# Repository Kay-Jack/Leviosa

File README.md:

# Photon

## Description

## Complete

## WIP

## Features

## Images
### PCB Front View

### PCB Back View

### Schematic 

## Version

## Repository
Hosted on GitHub: [AirMatress/Photon](https://github.com/AirMatress/Photon)

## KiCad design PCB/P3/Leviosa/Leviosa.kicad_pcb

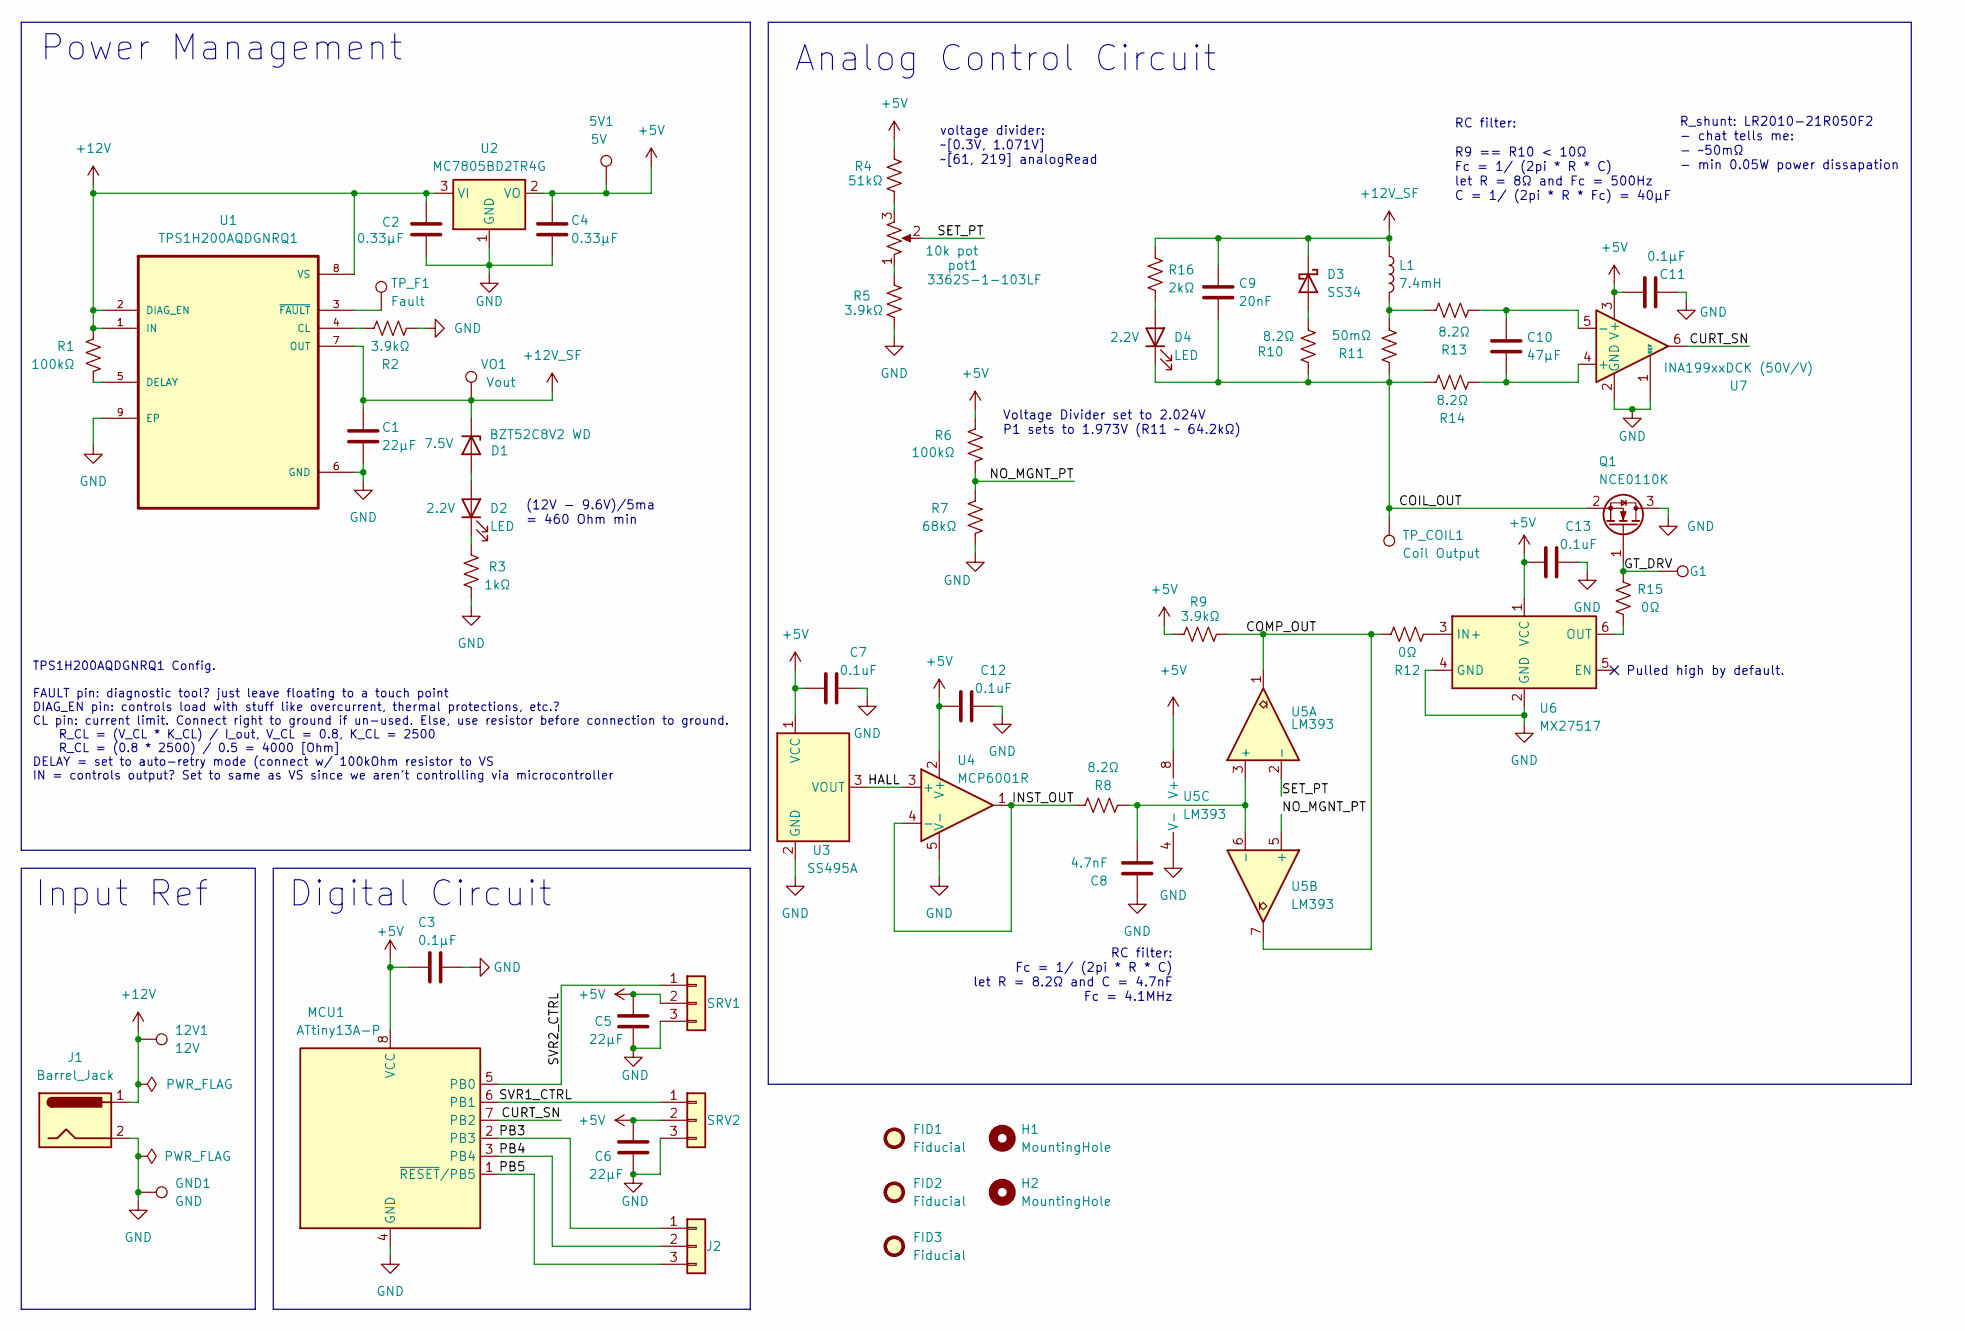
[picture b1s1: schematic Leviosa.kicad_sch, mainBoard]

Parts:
5V1: 5V; TestPoint_Pad_D1.5mm
12V1: 12V; TestPoint_Pad_D1.0mm
C1, C5, C6: 22µF; C_0805_2012Metric
C2, C4: 0.33µF; C_0805_2012Metric
C3, C11: 0.1µF; C_0603_1608Metric
C7, C12, C13: 0.1uF; C_0603_1608Metric
C8: 4.7nF; C_0805_2012Metric_Pad1.18x1.45mm_HandSolder
C9: 20nF; C_0805_2012Metric_Pad1.18x1.45mm_HandSolder
C10: 47μF; C_1206_3216Metric
D1: BZT52C8V2 WD; D_SOD-123
D2, D4: LED; LED_0805_2012Metric; PARTREV 16
D3: SS34; D_SOD-323
FID1, FID2, FID3: Fiducial; Fiducial_0.5mm_Mask1mm
G1: set_point_trigger; TestPoint_Pad_D1.0mm
GND1: GND; TestPoint_Pad_D1.0mm
H1, H2: MountingHole; MountingHole_3.2mm_M3_ISO7380
J1: Barrel_Jack; BarrelJack_Kycon_KLDX-0202-xC_Horizontal
J2: 2.54mm 1x03 Spare; PinHeader_1x03_P2.54mm_Vertical
L1: 7.4mH; PinHeader_2x01_P2.54mm_Vertical
MCU1: ATtiny13A-P; DIP-8_W7.62mm
Q1: NCE0110K; TO-252-2
R1, R6: 100kΩ; R_0603_1608Metric
R2, R5, R9: 3.9kΩ; R_0603_1608Metric
R3: 1kΩ; R_0603_1608Metric
R4: 51kΩ; R_0603_1608Metric
R7: 68kΩ; R_0603_1608Metric
R8, R10, R13, R14: 8.2Ω; R_1206_3216Metric
R11: 50mΩ; R_2010_5025Metric
R12, R15: 0Ω; R_0603_1608Metric
R16: 2kΩ; R_0603_1608Metric
SRV1, SRV2: 2.54mm 1x03 Servo 1; PinHeader_1x03_P2.54mm_Vertical
TP_COIL1: Coil Output; TestPoint_Pad_D1.0mm
TP_F1: Fault; TestPoint_Pad_D1.0mm
U1: TPS1H200AQDGNRQ1; SOP65P490X110-9N
U2: MC7805BD2TR4G; TO-263-2
U3: SS495A; PinHeader_1x03_P2.54mm_Vertical
U4: MCP6001R; SOT-23-5
U5: LM393; SOIC-8_3.9x4.9mm_P1.27mm
U6: MX27517; SOT-23-6
U7: INA199xxDCK (50V/V); SOT-363_SC-70-6
VO1: Vout; TestPoint_Pad_D1.0mm
pot1: 3362S-1-103LF; Potentiometer_ACP_CA6-H2,5_Horizontal

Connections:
+5V: 5V1.1, C3.1, C4.1, C5.1, C6.1, C7.1, C11.1, C12.1, C13.1, MCU1.8 (VCC), R4.2, R6.2, R9.2, SRV1.2, SRV2.2, U2.2 (VO), U3.1 (VCC), U4.2 (V+), U5.8 (V+), U6.1 (VCC), U7.3 (V+)
+12V: 12V1.1, C2.1, J1.1, R1.2, U1.1 (IN), U1.2 (DIAG_EN), U1.8 (VS), U2.3 (VI)
+12V_SF: C1.1, C9.1, D1.1 (K), D3.1 (K), L1.1, R16.1, U1.7 (OUT), VO1.1
/COIL_OUT: C9.2, D4.1 (K), Q1.2 (S), R10.2, R11.2, R14.1, TP_COIL1.1
/COMP_OUT: R9.1, R12.1, U5.1, U5.7
/CURT_SN: MCU1.7 (PB2), U7.6
/GT_DRV: G1.1, Q1.1 (G), R15.2
/HALL: U3.3 (VOUT), U4.3 (+)
/INST_OUT: R8.1, U4.1, U4.4 (-)
/NO_MGNT_PT: R6.1, R7.2, U5.5 (+)
/PB3: J2.1, MCU1.2 (PB3)
/PB4: J2.2, MCU1.3 (PB4)
/PB5: J2.3, MCU1.1 (~RESET/PB5)
/SET_PT: U5.2 (-), pot1.2
/SVR1_CTRL: MCU1.6 (PB1), SRV2.1
/SVR2_CTRL: MCU1.5 (PB0), SRV1.1
GND: C1.2, C2.2, C3.2, C4.2, C5.2, C6.2, C7.2, C8.1, C11.2, C12.2, C13.2, GND1.1, J1.2, MCU1.4 (GND), Q1.3 (D), R2.1, R3.2, R5.1, R7.1, SRV1.3, SRV2.3, U1.6 (GND), U1.9 (EP), U2.1 (GND), U3.2 (GND), U4.5 (V-), U5.4 (V-), U6.2 (GND), U6.4 (GND), U7.1 (REF), U7.2 (GND)
unnamed: D1.2 (A), D2.2 (A)
unnamed: D2.1 (K), R3.1
unnamed: D3.2 (A), R10.1
unnamed: D4.2 (A), R16.2
unnamed: L1.2, R11.1, R13.1
unnamed: R4.1, pot1.3
unnamed: R5.2, pot1.1
unnamed: R2.2, U1.4 (CL)
unnamed: R1.1, U1.5 (DELAY)
unnamed: TP_F1.1, U1.3 (~FAULT)
unnamed: C8.2, R8.2, U5.3 (+), U5.6 (-)
unnamed: R12.2, U6.3 (IN+)
unnamed: R15.1, U6.6 (OUT)
unnamed: C10.1, R14.2, U7.4 (+)
unnamed: C10.2, R13.2, U7.5 (-)

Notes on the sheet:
Power Management
RC filter: R9 == R10 < 10Ω Fc = 1/ (2pi * R * C) let R = 8Ω and Fc = 500Hz C = 1/ (2pi * R * Fc) = 40μF
R_shunt: LR2010-21R050F2 - chat tells me: - ~50mΩ - min 0.05W power dissapation
Input Ref
Analog Control Circuit
(12V - 9.6V)/5ma = 460 Ohm min
TPS1H200AQDGNRQ1 Config. FAULT pin: diagnostic tool? just leave floating to a touch point DIAG_EN pin: controls load with stuff like overcurrent, thermal protections, etc.? CL pin: current limit. Connect right to ground if un-used. Else, use resistor before connection to ground. R_CL = (V_CL * K_CL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
Digital Circuit
Pulled high by default.
voltage divider: ~[0.3V, 1.071V] ~[61, 219] analogRead
RC filter: Fc = 1/ (2pi * R * C) let R = 8.2Ω and C = 4.7nF Fc = 4.1MHz
Voltage Divider set to 2.024V P1 sets to 1.973V (R11 ~ 64.2kΩ)

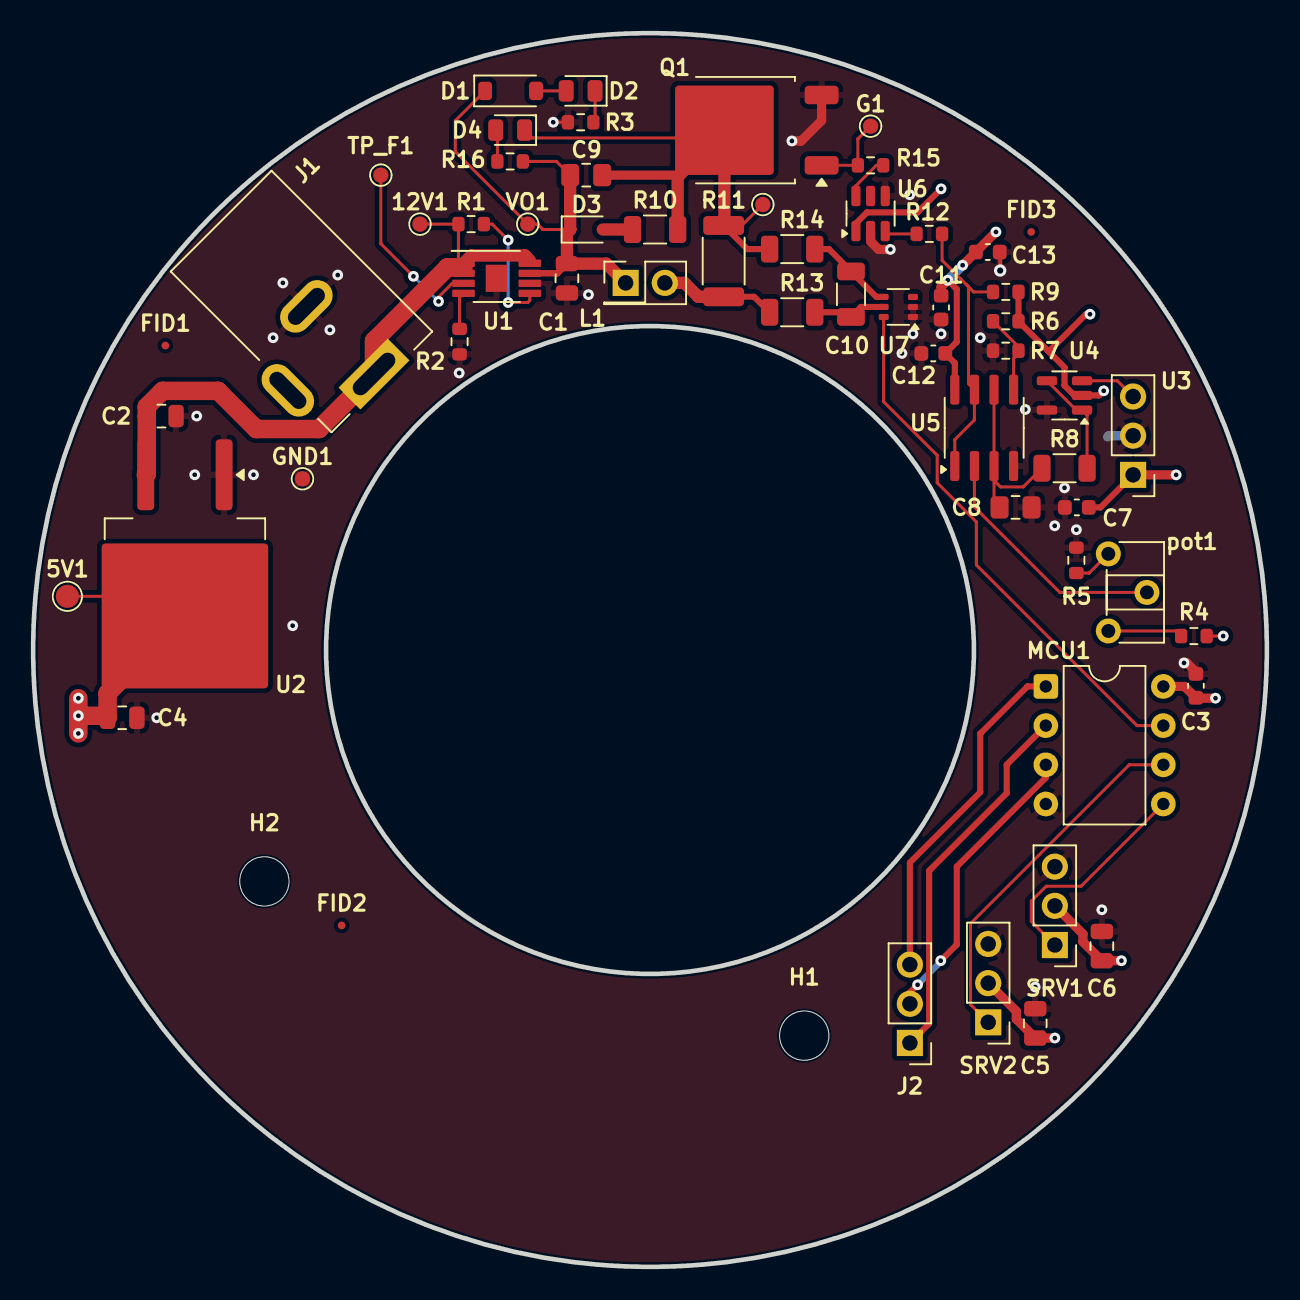
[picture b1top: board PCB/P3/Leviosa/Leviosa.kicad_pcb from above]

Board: 2 copper layers, 80.0 x 80.0 mm, 60 parts (0 on the bottom side), 32 nets.

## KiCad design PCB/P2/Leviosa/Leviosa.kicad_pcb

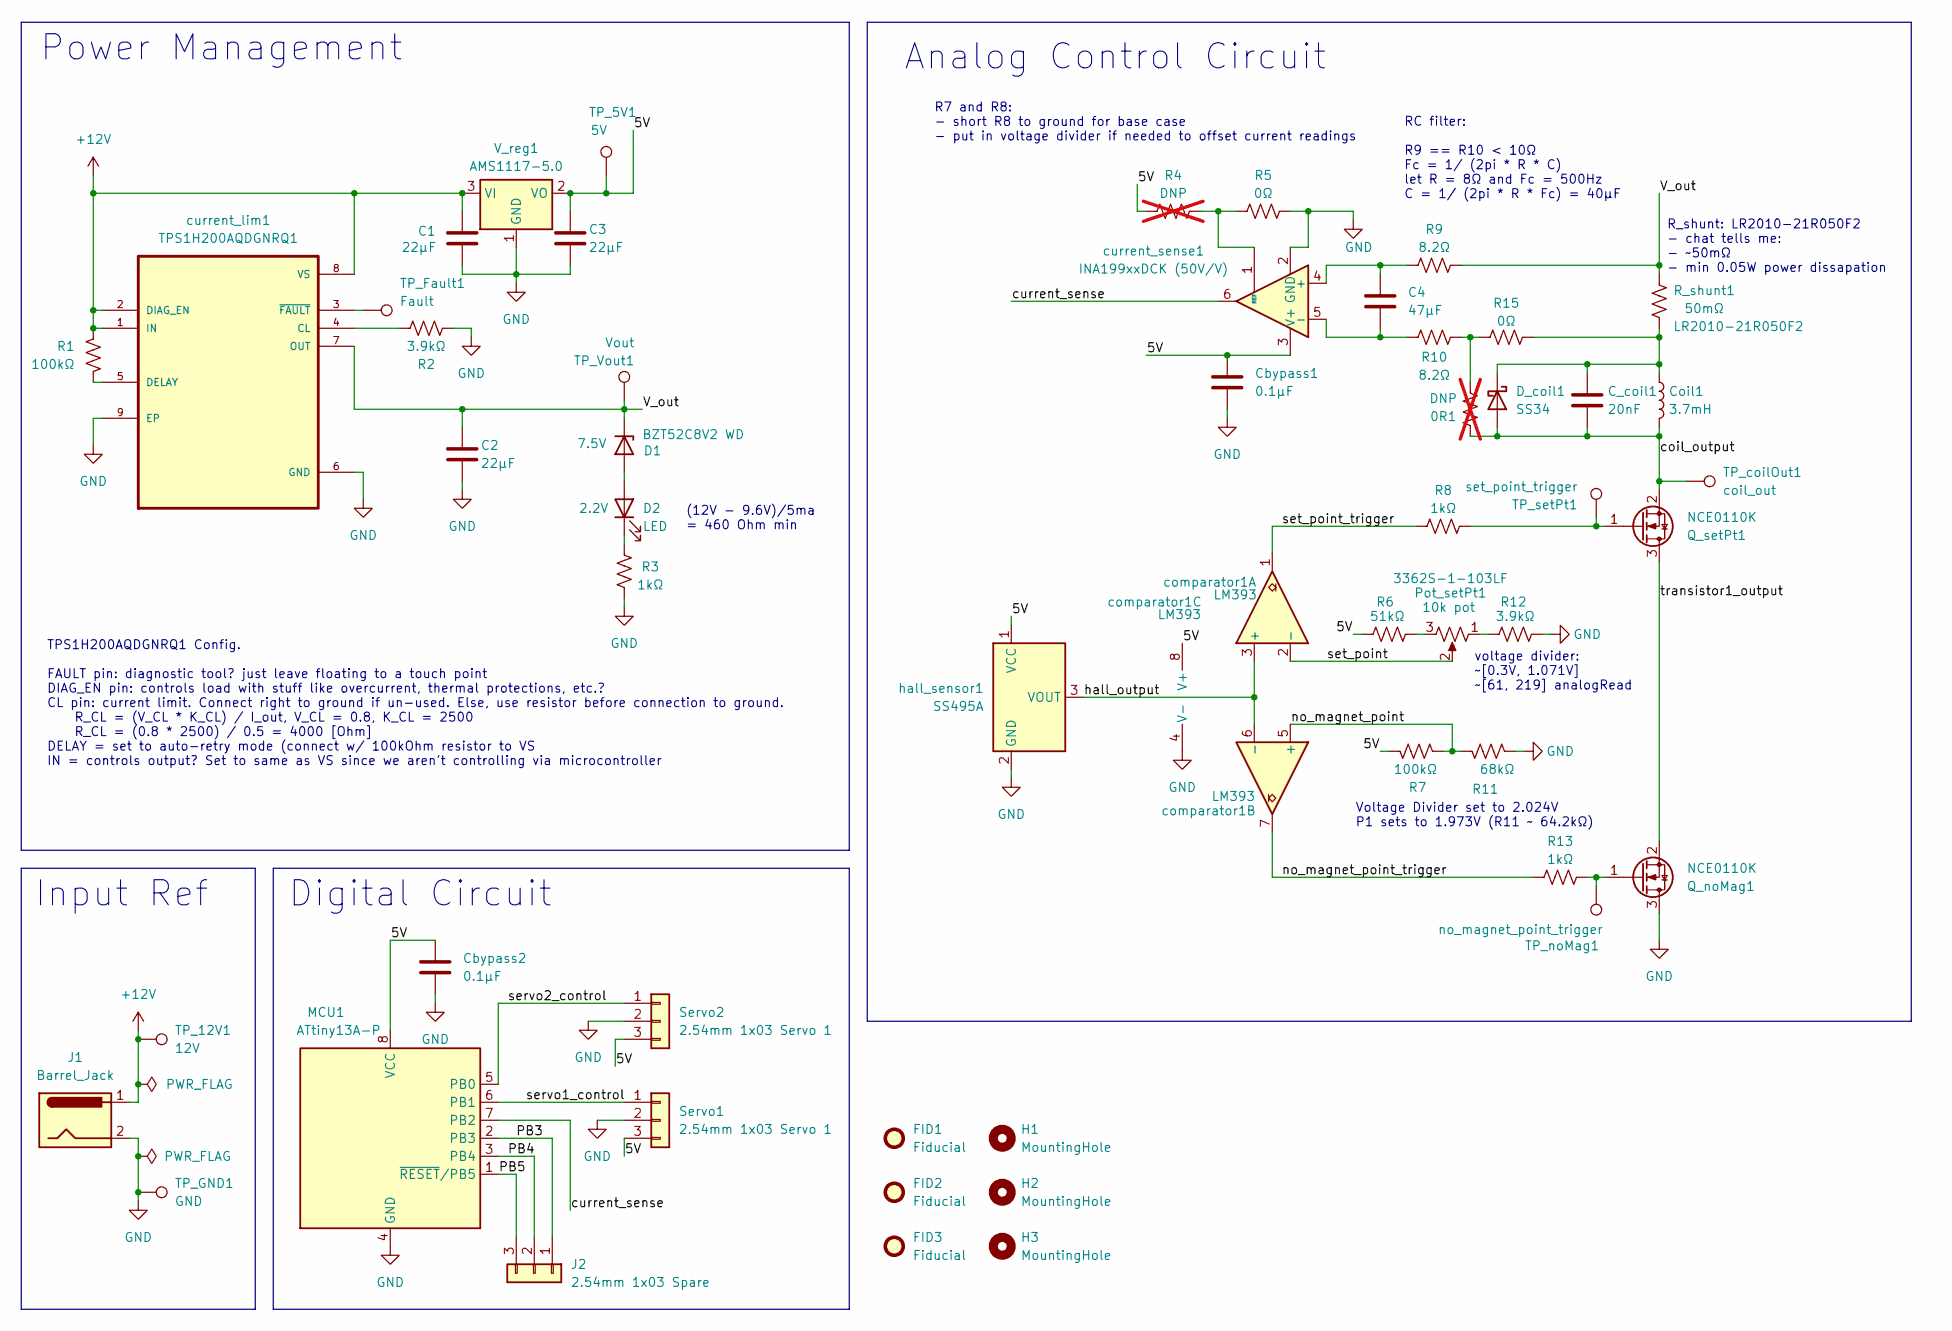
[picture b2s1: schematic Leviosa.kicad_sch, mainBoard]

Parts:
0R1: DNP; R_0603_1608Metric; not fitted
C1, C2, C3: 22µF; C_0805_2012Metric
C4: 47μF; C_1206_3216Metric
C_coil1: 20nF; C_0805_2012Metric_Pad1.18x1.45mm_HandSolder
Cbypass1, Cbypass2: 0.1µF; C_0402_1005Metric
Coil1: 3.7mH; L_Axial_L5.0mm_D3.6mm_P10.00mm_Horizontal_Murata_BL01RN1A2A2
D1: BZT52C8V2 WD; D_SOD-123
D2: LED; LED_0805_2012Metric; PARTREV 16
D_coil1: SS34; D_SMA
FID1, FID2, FID3: Fiducial; Fiducial_0.5mm_Mask1mm
H1, H2, H3: MountingHole; MountingHole_3.2mm_M3_ISO7380
J1: Barrel_Jack; BarrelJack_Kycon_KLDX-0202-xC_Horizontal
J2: 2.54mm 1x03 Spare; PinHeader_1x03_P2.54mm_Vertical
MCU1: ATtiny13A-P; DIP-8_W7.62mm
Pot_setPt1: 3362S-1-103LF; Potentiometer_ACP_CA6-H2,5_Horizontal
Q_noMag1: NCE0110K; TO-252-2
Q_setPt1: NCE0110K; TO-252-2
R1, R7: 100kΩ; R_0805_2012Metric_Pad1.20x1.40mm_HandSolder
R2, R12: 3.9kΩ; R_0603_1608Metric
R3, R8, R13: 1kΩ; R_0805_2012Metric_Pad1.20x1.40mm_HandSolder
R4: DNP; R_0603_1608Metric; not fitted
R5, R15: 0Ω; R_0603_1608Metric
R6: 51kΩ; R_0603_1608Metric
R9, R10: 8.2Ω; R_1206_3216Metric
R11: 68kΩ; R_0603_1608Metric
R_shunt1: 50mΩ; R_2010_5025Metric
Servo1, Servo2: 2.54mm 1x03 Servo 1; PinHeader_1x03_P2.54mm_Vertical
TP_5V1: 5V; TestPoint_Pad_D1.5mm
TP_12V1: 12V; TestPoint_Pad_D1.5mm
TP_Fault1: Fault; TestPoint_Pad_D1.5mm
TP_GND1: GND; TestPoint_Pad_D1.5mm
TP_Vout1: Vout; TestPoint_Pad_D1.5mm
TP_coilOut1: coil_out; TestPoint_Pad_D1.5mm
TP_noMag1: no_magnet_point_trigger; TestPoint_Pad_D1.5mm
TP_setPt1: set_point_trigger; TestPoint_Pad_D1.5mm
V_reg1: AMS1117-5.0; SOT-223-3_TabPin2
comparator1: LM393; SOIC-8_5.3x5.3mm_P1.27mm
current_lim1: TPS1H200AQDGNRQ1; SOP65P490X110-9N
current_sense1: INA199xxDCK (50V/V); SOT-363_SC-70-6
hall_sensor1: SS495A; PinHeader_1x03_P2.54mm_Vertical

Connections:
+12V: C1.1, J1.1, R1.2, TP_12V1.1, V_reg1.3 (VI), current_lim1.1 (IN), current_lim1.2 (DIAG_EN), current_lim1.8 (VS)
/5V: C3.1, Cbypass1.1, Cbypass2.1, MCU1.8 (VCC), R4.2, R6.2, R7.2, Servo1.3, Servo2.3, TP_5V1.1, V_reg1.2 (VO), comparator1.8 (V+), current_sense1.3 (V+), hall_sensor1.1 (VCC)
/PB3: J2.1, MCU1.2 (PB3)
/PB4: J2.2, MCU1.3 (PB4)
/PB5: J2.3, MCU1.1 (~RESET/PB5)
/V_out: C2.1, D1.1 (K), R9.1, R_shunt1.2, TP_Vout1.1, current_lim1.7 (OUT)
/coil_output: 0R1.2, C_coil1.2, Coil1.2, D_coil1.2 (A), Q_setPt1.2 (S), TP_coilOut1.1
/current_sense: MCU1.7 (PB2), current_sense1.6
/hall_output: comparator1.3 (+), comparator1.6 (-), hall_sensor1.3 (VOUT)
/no_magnet_point: R7.1, R11.2, comparator1.5 (+)
/no_magnet_point_trigger: R13.2, comparator1.7
/servo1_control: MCU1.6 (PB1), Servo1.1
/servo2_control: MCU1.5 (PB0), Servo2.1
/set_point: Pot_setPt1.2, comparator1.2 (-)
/set_point_trigger: R8.2, comparator1.1
/transistor1_output: Q_noMag1.2 (S), Q_setPt1.3 (D)
GND: C1.2, C2.2, C3.2, Cbypass1.2, Cbypass2.2, J1.2, MCU1.4 (GND), Q_noMag1.3 (D), R2.1, R3.2, R5.1, R11.1, R12.1, Servo1.2, Servo2.2, TP_GND1.1, V_reg1.1 (GND), comparator1.4 (V-), current_lim1.6 (GND), current_lim1.9 (EP), current_sense1.2 (GND), hall_sensor1.2 (GND)
unnamed: 0R1.1, R10.1, R15.2
unnamed: D1.2 (A), D2.2 (A)
unnamed: D2.1 (K), R3.1
unnamed: C_coil1.1, Coil1.1, D_coil1.1 (K), R15.1, R_shunt1.1
unnamed: Pot_setPt1.1, R12.2
unnamed: Pot_setPt1.3, R6.1
unnamed: Q_noMag1.1 (G), R13.1, TP_noMag1.1
unnamed: Q_setPt1.1 (G), R8.1, TP_setPt1.1
unnamed: R2.2, current_lim1.4 (CL)
unnamed: R1.1, current_lim1.5 (DELAY)
unnamed: TP_Fault1.1, current_lim1.3 (~FAULT)
unnamed: C4.1, R9.2, current_sense1.4 (+)
unnamed: C4.2, R10.2, current_sense1.5 (-)
unnamed: R4.1, R5.2, current_sense1.1 (REF)

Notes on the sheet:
Power Management
RC filter: R9 == R10 < 10Ω Fc = 1/ (2pi * R * C) let R = 8Ω and Fc = 500Hz C = 1/ (2pi * R * Fc) = 40μF
R_shunt: LR2010-21R050F2 - chat tells me: - ~50mΩ - min 0.05W power dissapation
Input Ref
R7 and R8: - short R8 to ground for base case - put in voltage divider if needed to offset current readings
Analog Control Circuit
(12V - 9.6V)/5ma = 460 Ohm min
TPS1H200AQDGNRQ1 Config. FAULT pin: diagnostic tool? just leave floating to a touch point DIAG_EN pin: controls load with stuff like overcurrent, thermal protections, etc.? CL pin: current limit. Connect right to ground if un-used. Else, use resistor before connection to ground. R_CL = (V_CL * K_CL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
Digital Circuit
Voltage Divider set to 2.024V P1 sets to 1.973V (R11 ~ 64.2kΩ)
voltage divider: ~[0.3V, 1.071V] ~[61, 219] analogRead

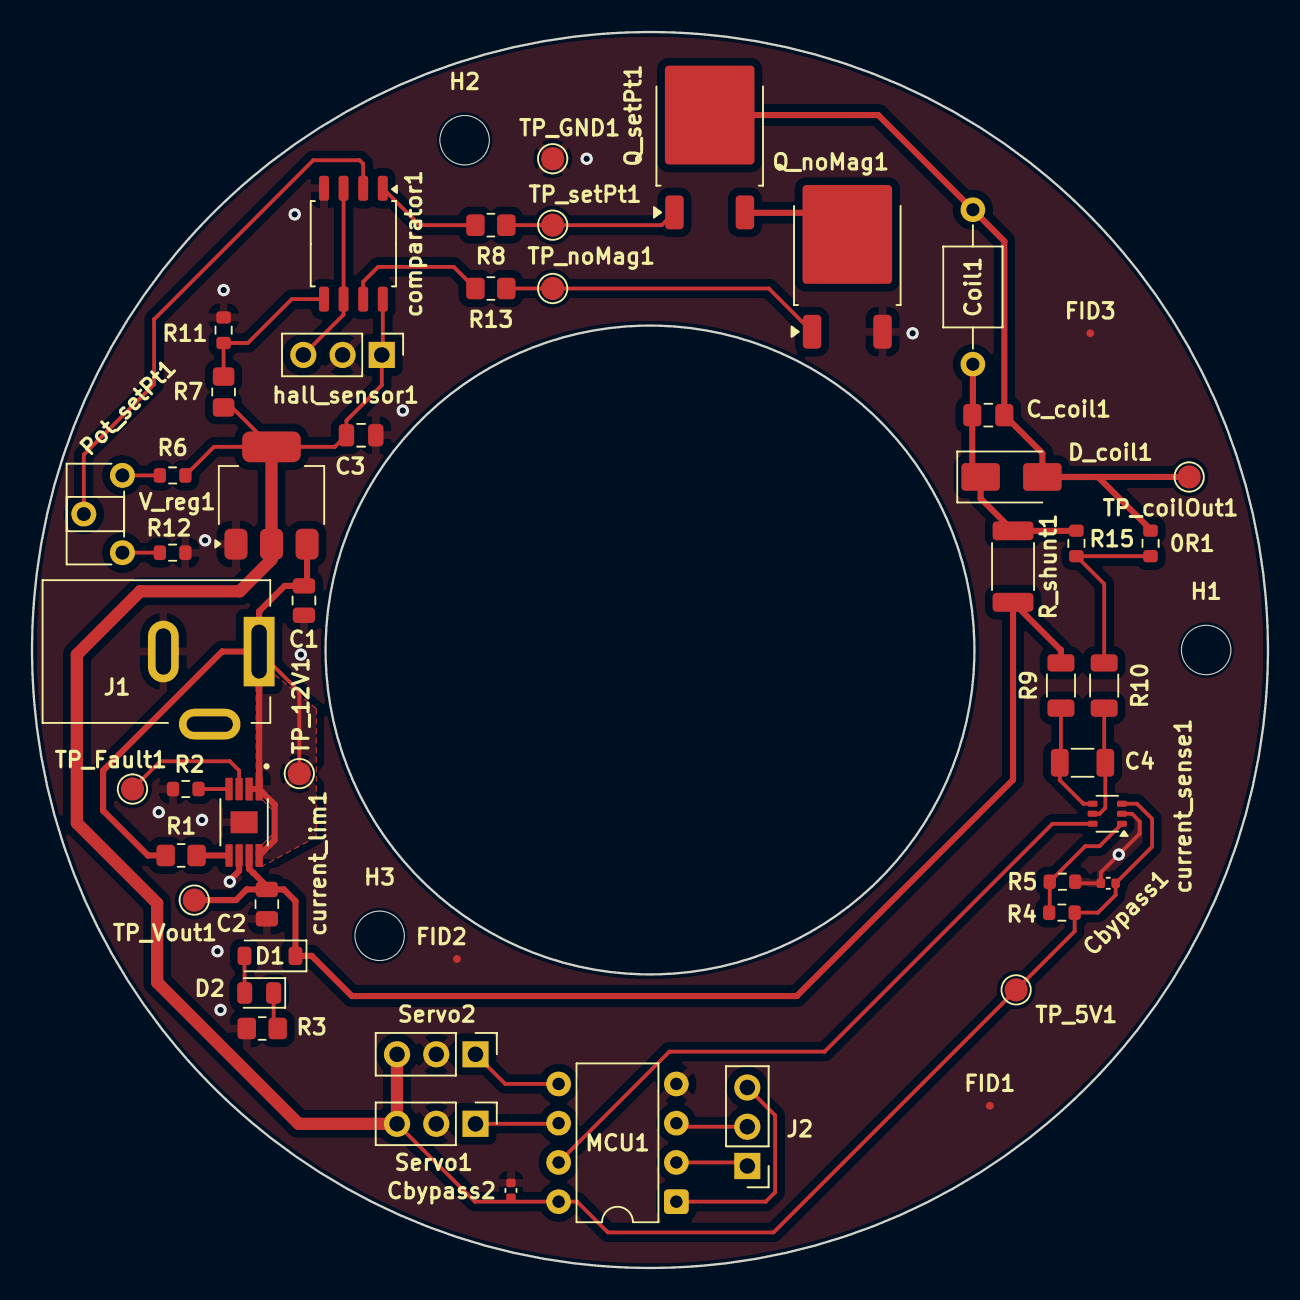
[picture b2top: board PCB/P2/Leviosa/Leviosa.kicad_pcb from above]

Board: 2 copper layers, 80.0 x 80.0 mm, 54 parts (0 on the bottom side), 31 nets.

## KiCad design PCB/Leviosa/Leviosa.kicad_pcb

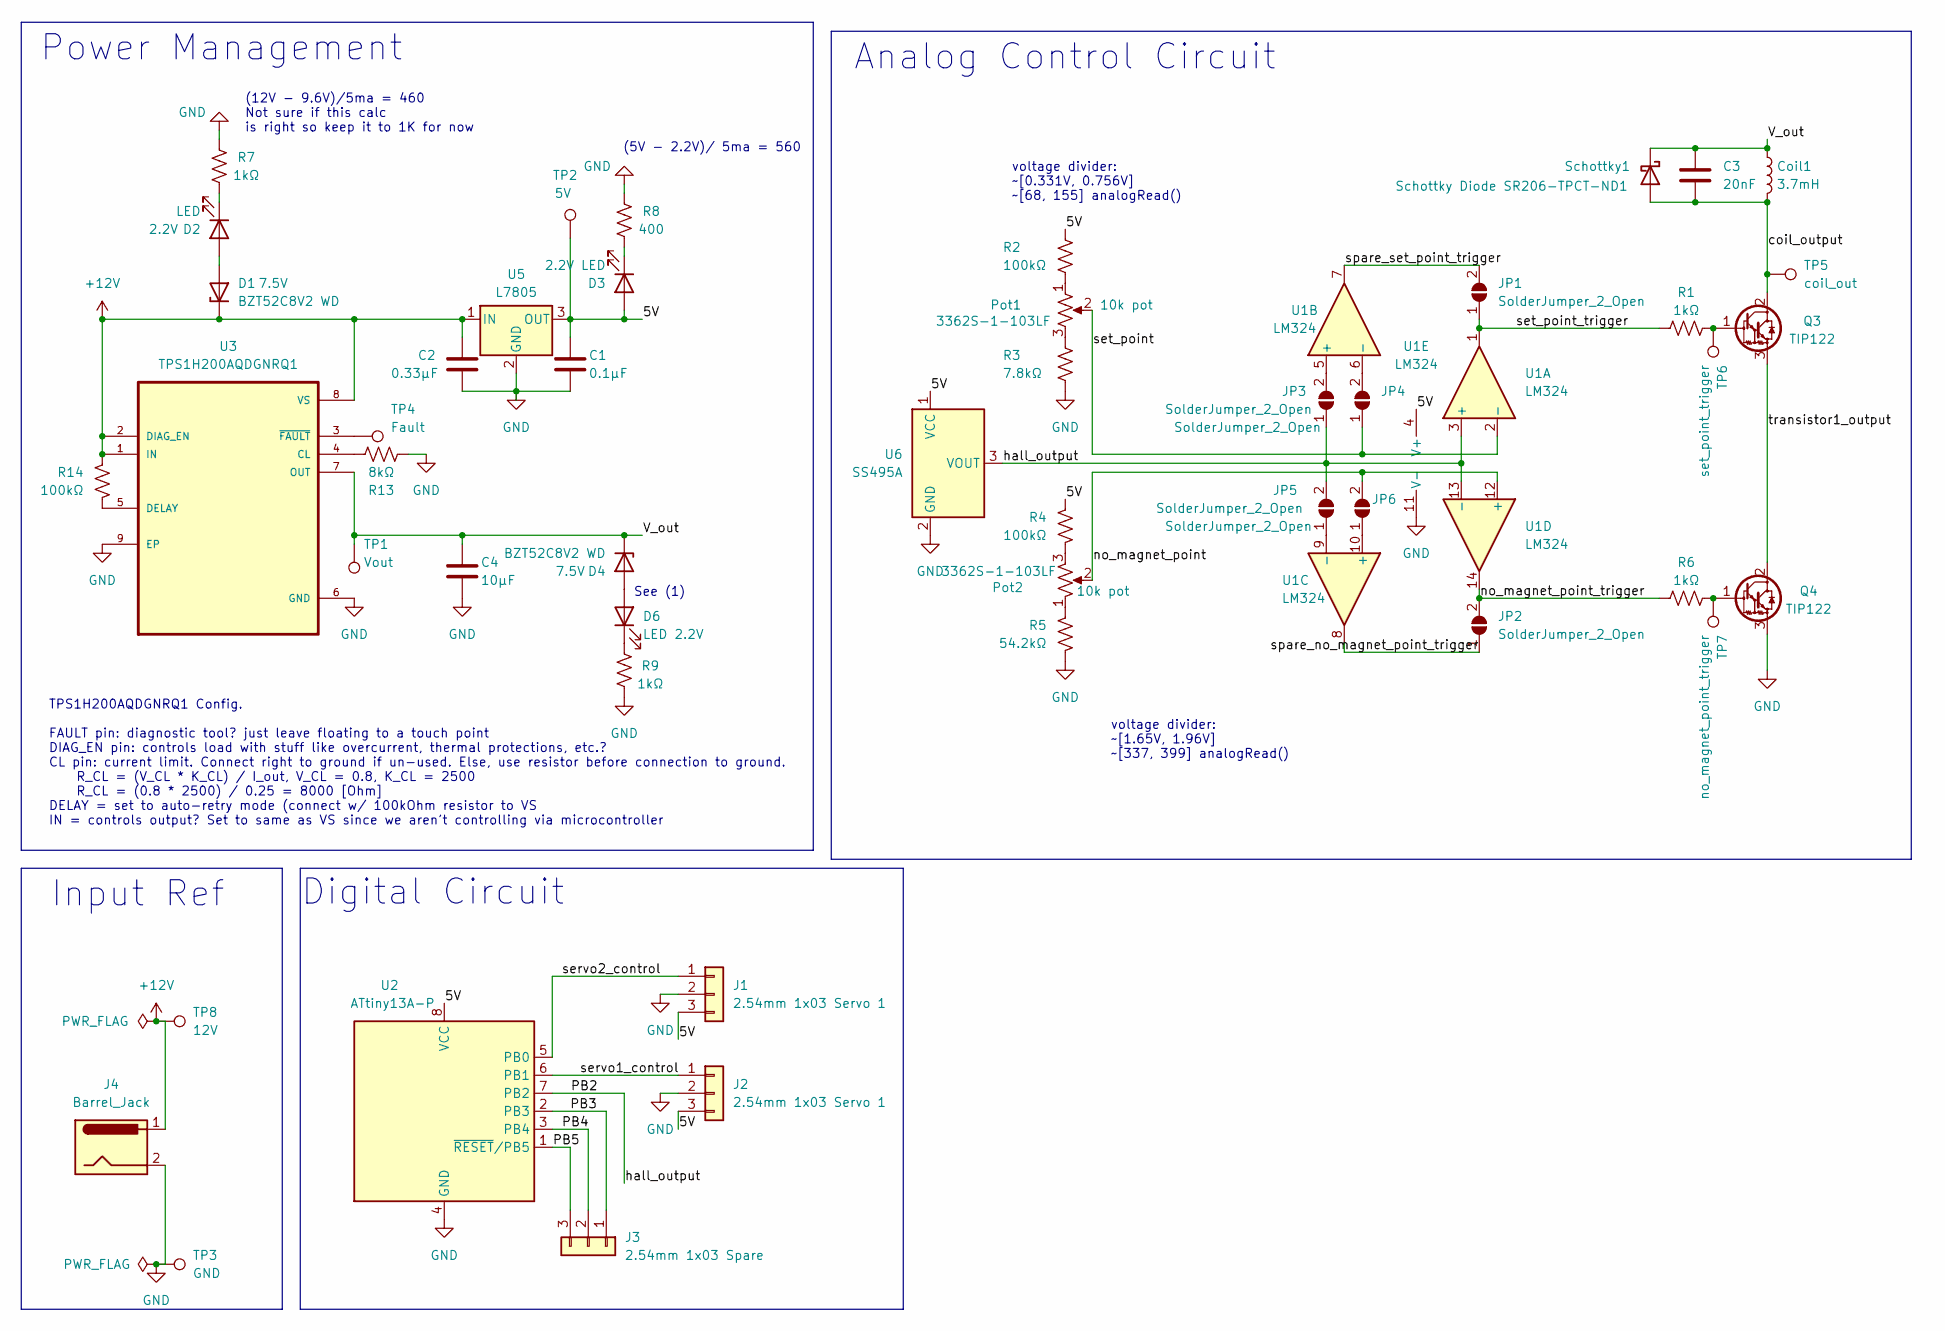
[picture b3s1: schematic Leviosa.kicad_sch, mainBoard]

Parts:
C1: 0.1µF; C_0805_2012Metric_Pad1.18x1.45mm_HandSolder
C2: 0.33µF; C_0805_2012Metric_Pad1.18x1.45mm_HandSolder
C3: 20nF; C_0805_2012Metric_Pad1.18x1.45mm_HandSolder
C4: 10µF; C_0805_2012Metric_Pad1.18x1.45mm_HandSolder
Coil1: 3.7mH; L_Axial_L5.0mm_D3.6mm_P10.00mm_Horizontal_Murata_BL01RN1A2A2
D1, D4: BZT52C8V2 WD; D_SOD-123
D2, D3, D6: LED; LED_0805_2012Metric; PARTREV 16
J1, J2: 2.54mm 1x03 Servo 1; PinHeader_1x03_P2.54mm_Horizontal
J3: 2.54mm 1x03 Spare; PinHeader_1x03_P2.54mm_Horizontal
J4: Barrel_Jack; BarrelJack_Kycon_KLDX-0202-xC_Horizontal
JP1, JP2, JP3, JP4, JP5, JP6: SolderJumper_2_Open; SolderJumper-2_P1.3mm_Open_Pad1.0x1.5mm
Pot1, Pot2: 3362S-1-103LF; Potentiometer_ACP_CA6-H2,5_Horizontal
Q3, Q4: TIP122; TO-220-3_Vertical
R1, R6, R7, R9: 1kΩ; R_0805_2012Metric_Pad1.20x1.40mm_HandSolder
R2, R4, R14: 100kΩ; R_0805_2012Metric_Pad1.20x1.40mm_HandSolder
R3: 7.8kΩ; R_0805_2012Metric_Pad1.20x1.40mm_HandSolder
R5: 54.2kΩ; R_0805_2012Metric_Pad1.20x1.40mm_HandSolder
R8: 400; R_0805_2012Metric_Pad1.20x1.40mm_HandSolder
R13: 8kΩ; R_0805_2012Metric_Pad1.20x1.40mm_HandSolder
Schottky1: Schottky Diode SR206-TPCT-ND1; SMA_DIO
TP1: Vout; TestPoint_Pad_D3.0mm
TP2: 5V; TestPoint_Pad_D3.0mm
TP3: GND; TestPoint_Pad_D3.0mm
TP4: Fault; TestPoint_Pad_D3.0mm
TP5: coil_out; TestPoint_Pad_D3.0mm
TP6: set_point_trigger; TestPoint_Pad_D3.0mm
TP7: no_magnet_point_trigger; TestPoint_Pad_D3.0mm
TP8: 12V; TestPoint_Pad_D3.0mm
U1: LM324; DIP-14_W7.62mm
U2: ATtiny13A-P; DIP-8_W7.62mm
U3: TPS1H200AQDGNRQ1; SOP65P490X110-9N
U5: L7805; PinHeader_1x03_P2.00mm_Vertical
U6: SS495A; PinHeader_1x03_P2.00mm_Vertical

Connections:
+12V: C2.1, D1.1 (K), J4.1, R14.2, TP8.1, U3.1 (IN), U3.2 (DIAG_EN), U3.8 (VS), U5.1 (IN)
/5V: C1.1, D3.2 (A), J1.3, J2.3, R2.2, R4.2, TP2.1, U1.4 (V+), U2.8 (VCC), U5.3 (OUT), U6.1 (VCC)
/PB2: JP3.1 (A), JP5.2 (B), U1.3 (+), U1.13 (-), U2.7 (PB2), U6.3 (VOUT)
/PB3: J3.1, U2.2 (PB3)
/PB4: J3.2, U2.3 (PB4)
/PB5: J3.3, U2.1 (~RESET/PB5)
/V_out: C3.1, C4.1, Coil1.1, D4.1 (K), Schottky1.1 (K), TP1.1, U3.7 (OUT)
/coil_output: C3.2, Coil1.2, Q3.2 (C), Schottky1.2 (A), TP5.1
/no_magnet_point: JP6.2 (B), Pot2.2, U1.12 (+)
/no_magnet_point_trigger: JP2.2 (B), R6.2, U1.14
/servo1_control: J2.1, U2.6 (PB1)
/servo2_control: J1.1, U2.5 (PB0)
/set_point: JP4.1 (A), Pot1.2, U1.2 (-)
/set_point_trigger: JP1.1 (A), R1.2, U1.1
/spare_no_magnet_point_trigger: JP2.1 (A), U1.8
/spare_set_point_trigger: JP1.2 (B), U1.7
/transistor1_output: Q3.3 (E), Q4.2 (C)
GND: C1.2, C2.2, C4.2, J1.2, J2.2, J4.2, Q4.3 (E), R3.1, R5.1, R7.2, R8.2, R9.2, R13.1, TP3.1, U1.11 (V-), U2.4 (GND), U3.6 (GND), U3.9 (EP), U5.2 (GND), U6.2 (GND)
unnamed: D1.2 (A), D2.2 (A)
unnamed: D2.1 (K), R7.1
unnamed: D3.1 (K), R8.1
unnamed: D4.2 (A), D6.2 (A)
unnamed: D6.1 (K), R9.1
unnamed: JP3.2 (B), U1.5 (+)
unnamed: JP4.2 (B), U1.6 (-)
unnamed: JP5.1 (A), U1.9 (-)
unnamed: JP6.1 (A), U1.10 (+)
unnamed: Pot1.1, R2.1
unnamed: Pot1.3, R3.2
unnamed: Pot2.1, R5.2
unnamed: Pot2.3, R4.1
unnamed: Q3.1 (B), R1.1, TP6.1
unnamed: Q4.1 (B), R6.1, TP7.1
unnamed: R13.2, U3.4 (CL)
unnamed: R14.1, U3.5 (DELAY)
unnamed: TP4.1, U3.3 (~FAULT)

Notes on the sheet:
Power Management
See (1)
Input Ref
Analog Control Circuit
(12V - 9.6V)/5ma = 460 Not sure if this calc is right so keep it to 1K for now
TPS1H200AQDGNRQ1 Config. FAULT pin: diagnostic tool? just leave floating to a touch point DIAG_EN pin: controls load with stuff like overcurrent, thermal protections, etc.? CL pin: current limit. Connect right to ground if un-used. Else, use resistor before connection to ground. R_CL = (V_CL * K_CL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
Digital Circuit
(5V - 2.2V)/ 5ma = 560
voltage divider: ~[1.65V, 1.96V] ~[337, 399] analogRead()
voltage divider: ~[0.331V, 0.756V] ~[68, 155] analogRead()

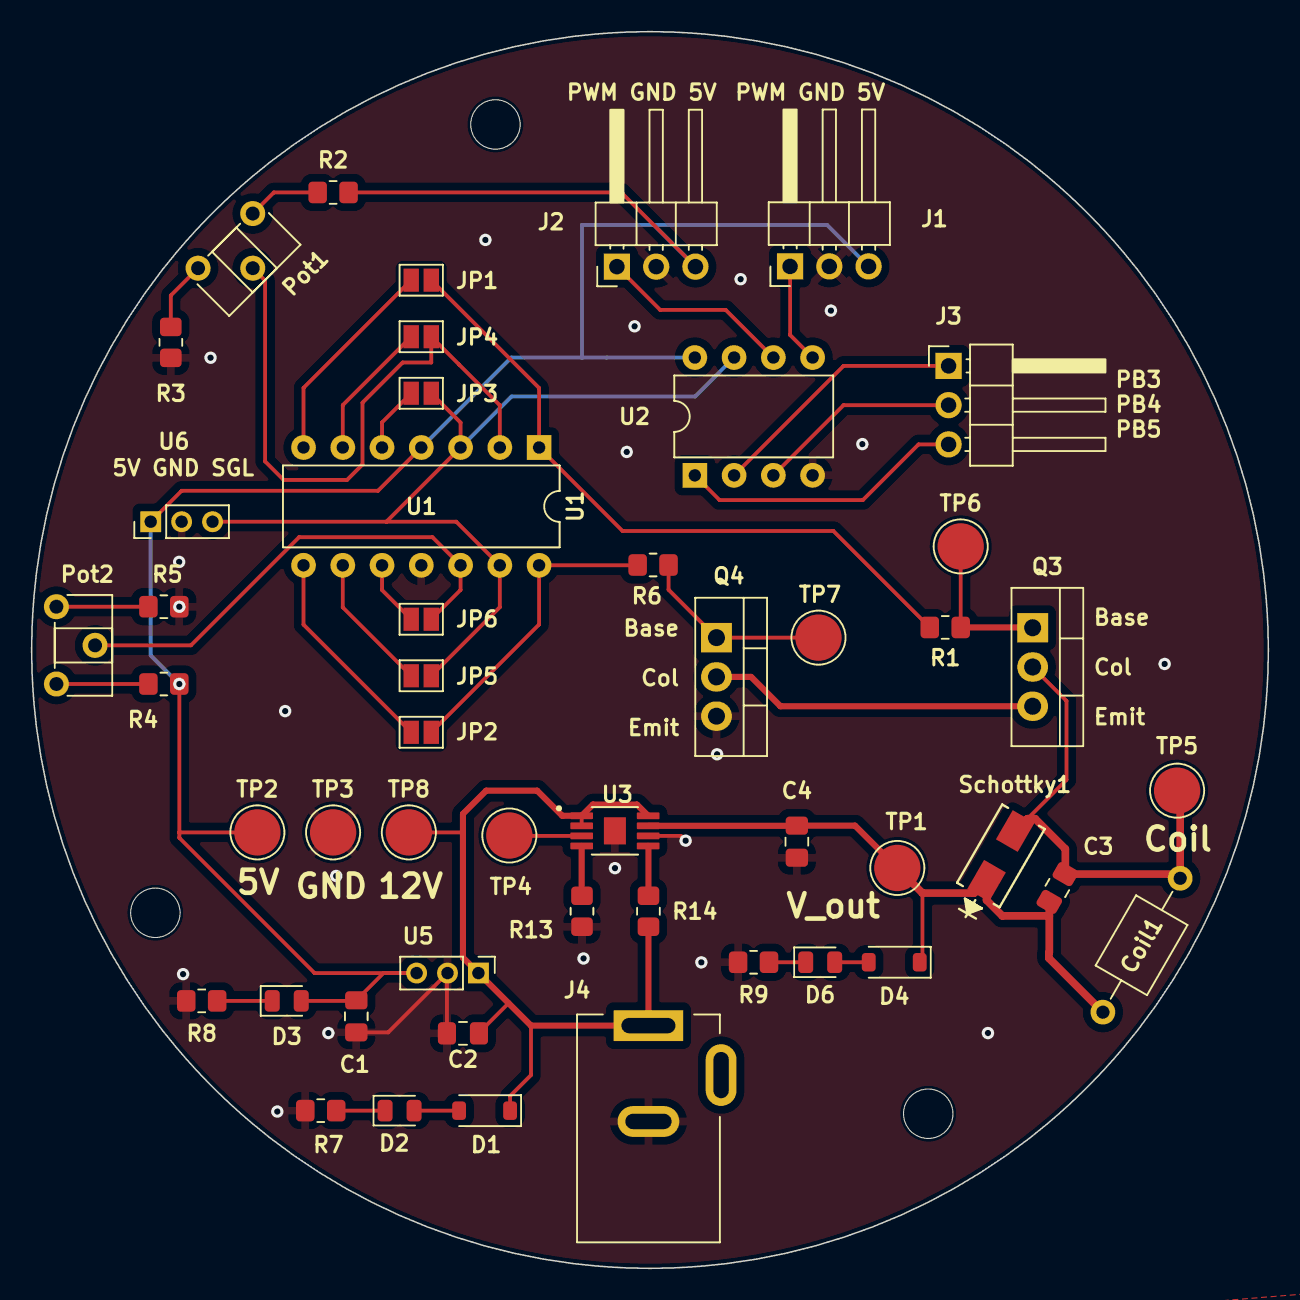
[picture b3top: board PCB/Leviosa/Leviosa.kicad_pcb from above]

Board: 2 copper layers, 80.0 x 80.0 mm, 52 parts (0 on the bottom side), 36 nets.

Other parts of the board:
H1, H2, H3: MountingHole; MountingHole_3.2mm_M3_ISO7380

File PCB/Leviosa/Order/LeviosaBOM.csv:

Reference,Qty,Value,Footprint,Datasheet,Link
C1,1,0.1µF,Capacitor_SMD:C_0805_2012Metric_Pad1.18x1.45mm_HandSolder,~,https://jlcpcb.com/partdetail/1943-CL10B104KB8NNNC/C1591
C2,1,0.33µF,Capacitor_SMD:C_0805_2012Metric_Pad1.18x1.45mm_HandSolder,~,https://jlcpcb.com/partdetail/74255-CL21B334KBFNNNE/C73142
C3,1,20nF,Capacitor_SMD:C_0805_2012Metric_Pad1.18x1.45mm_HandSolder,~,https://jlcpcb.com/partdetail/1954-0603B203K500NT/C1602
C4,1,10µF,Capacitor_SMD:C_0805_2012Metric_Pad1.18x1.45mm_HandSolder,~,
Coil1,1,3.7mH,Inductor_THT:L_Axial_L5.0mm_D3.6mm_P10.00mm_Horizontal_Murata_BL01RN1A2A2,https://www.aliexpress.com/item/32897928370.html?spm=a2g0o.o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,
"D1,D4",2,BZT52C8V2 WD,Diode_SMD:D_SOD-123,https://jlcpcb.com/partdetail/2479-BZT52C8V2WD/C2122,
"D2,D3,D6",3,LED,LED_SMD:LED_0805_2012Metric,~,
"J1,J2",2,2.54mm 1x03 Servo 1,Connector_PinHeader_2.54mm:PinHeader_1x03_P2.54mm_Horizontal,~,
J3,1,2.54mm 1x03 Spare,Connector_PinHeader_2.54mm:PinHeader_1x03_P2.54mm_Horizontal,~,
J4,1,Barrel_Jack,Connector_BarrelJack:BarrelJack_Kycon_KLDX-0202-xC_Horizontal,https://jlcpcb.com/partdetail/16896-DC_005_20/C16214,
"JP1,JP2,JP3,JP4,JP5,JP6",6,SolderJumper_2_Open,Jumper:SolderJumper-2_P1.3mm_Open_Pad1.0x1.5mm,~,
"Pot1,Pot2",2,3362S-1-103LF,"Potentiometer_THT:Potentiometer_ACP_CA6-H2,5_Horizontal",https://jlcpcb.com/api/file/downloadByFileSystemAccessId/858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,https://jlcpcb.com/partdetail/BOURNS-3362S_1103LF/C81272
"Q3,Q4",2,TIP122,Package_TO_SOT_THT:TO-220-3_Vertical,https://www.onsemi.com/pub/Collateral/TIP120-D.PDF,https://jlcpcb.com/partdetail/STMicroelectronics-TIP122/C16283
"R1,R6,R7,R9",4,1kΩ,Resistor_SMD:R_0805_2012Metric_Pad1.20x1.40mm_HandSolder,~,
"R2,R4,R14",3,100kΩ,Resistor_SMD:R_0805_2012Metric_Pad1.20x1.40mm_HandSolder,~,https://jlcpcb.com/partdetail/738376-RCT06100KFLF/C702843
R3,1,7.8kΩ,Resistor_SMD:R_0805_2012Metric_Pad1.20x1.40mm_HandSolder,~,
R5,1,54.2kΩ,Resistor_SMD:R_0805_2012Metric_Pad1.20x1.40mm_HandSolder,~,https://jlcpcb.com/partdetail/YAGEO-RT0402BRD0754K2L/C852840
R8,1,400,Resistor_SMD:R_0805_2012Metric_Pad1.20x1.40mm_HandSolder,~,
R13,1,8kΩ,Resistor_SMD:R_0805_2012Metric_Pad1.20x1.40mm_HandSolder,~,
Schottky1,1,Schottky Diode SR206-TPCT-ND1,B230A_13_F:SMA_DIO,https://jlcpcb.com/api/file/downloadByFileSystemAccessId/856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,https://jlcpcb.com/partdetail/DiodesIncorporated-B230A_13F/C12889
TP1,1,Vout,TestPoint:TestPoint_Pad_D3.0mm,~,
TP2,1,5V,TestPoint:TestPoint_Pad_D3.0mm,~,
TP3,1,GND,TestPoint:TestPoint_Pad_D3.0mm,~,
TP4,1,Fault,TestPoint:TestPoint_Pad_D3.0mm,~,
TP5,1,coil_out,TestPoint:TestPoint_Pad_D3.0mm,~,
TP6,1,set_point_trigger,TestPoint:TestPoint_Pad_D3.0mm,~,
TP7,1,no_magnet_point_trigger,TestPoint:TestPoint_Pad_D3.0mm,~,
TP8,1,12V,TestPoint:TestPoint_Pad_D3.0mm,~,
U1,1,LM324,Package_DIP:DIP-14_W7.62mm,http://www.ti.com/lit/ds/symlink/lm2902-n.pdf,https://jlcpcb.com/partdetail/TexasInstruments-LM324NNOPB/C352847
U2,1,ATtiny13A-P,Package_DIP:DIP-8_W7.62mm,http://ww1.microchip.com/downloads/en/DeviceDoc/doc8126.pdf,
U3,1,TPS1H200AQDGNRQ1,TPS1H200AQDGNRQ1:SOP65P490X110-9N,https://www.ti.com/general/docs/suppproductinfo.tsp?distId=1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,https://jlcpcb.com/partdetail/TexasInstruments-TPS1H200AQDGN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
U5,1,L7805,Connector_PinHeader_2.00mm:PinHeader_1x03_P2.00mm_Vertical,http://www.st.com/content/ccc/resource/technical/document/da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,https://jlcpcb.com/partdetail/STMicroelectronics-L7805CVDG/C3795
U6,1,SS495A,Connector_PinHeader_2.00mm:PinHeader_1x03_P2.00mm_Vertical,https://docs.rs-online.com/dc97/0900766b8009a37c.pdf,https://jlcpcb.com/partdetail/Honeywell-SS495A/C126668
